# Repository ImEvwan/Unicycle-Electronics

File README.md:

# Unicycle-Electronics
Accessory and support electronics for the unicycle project

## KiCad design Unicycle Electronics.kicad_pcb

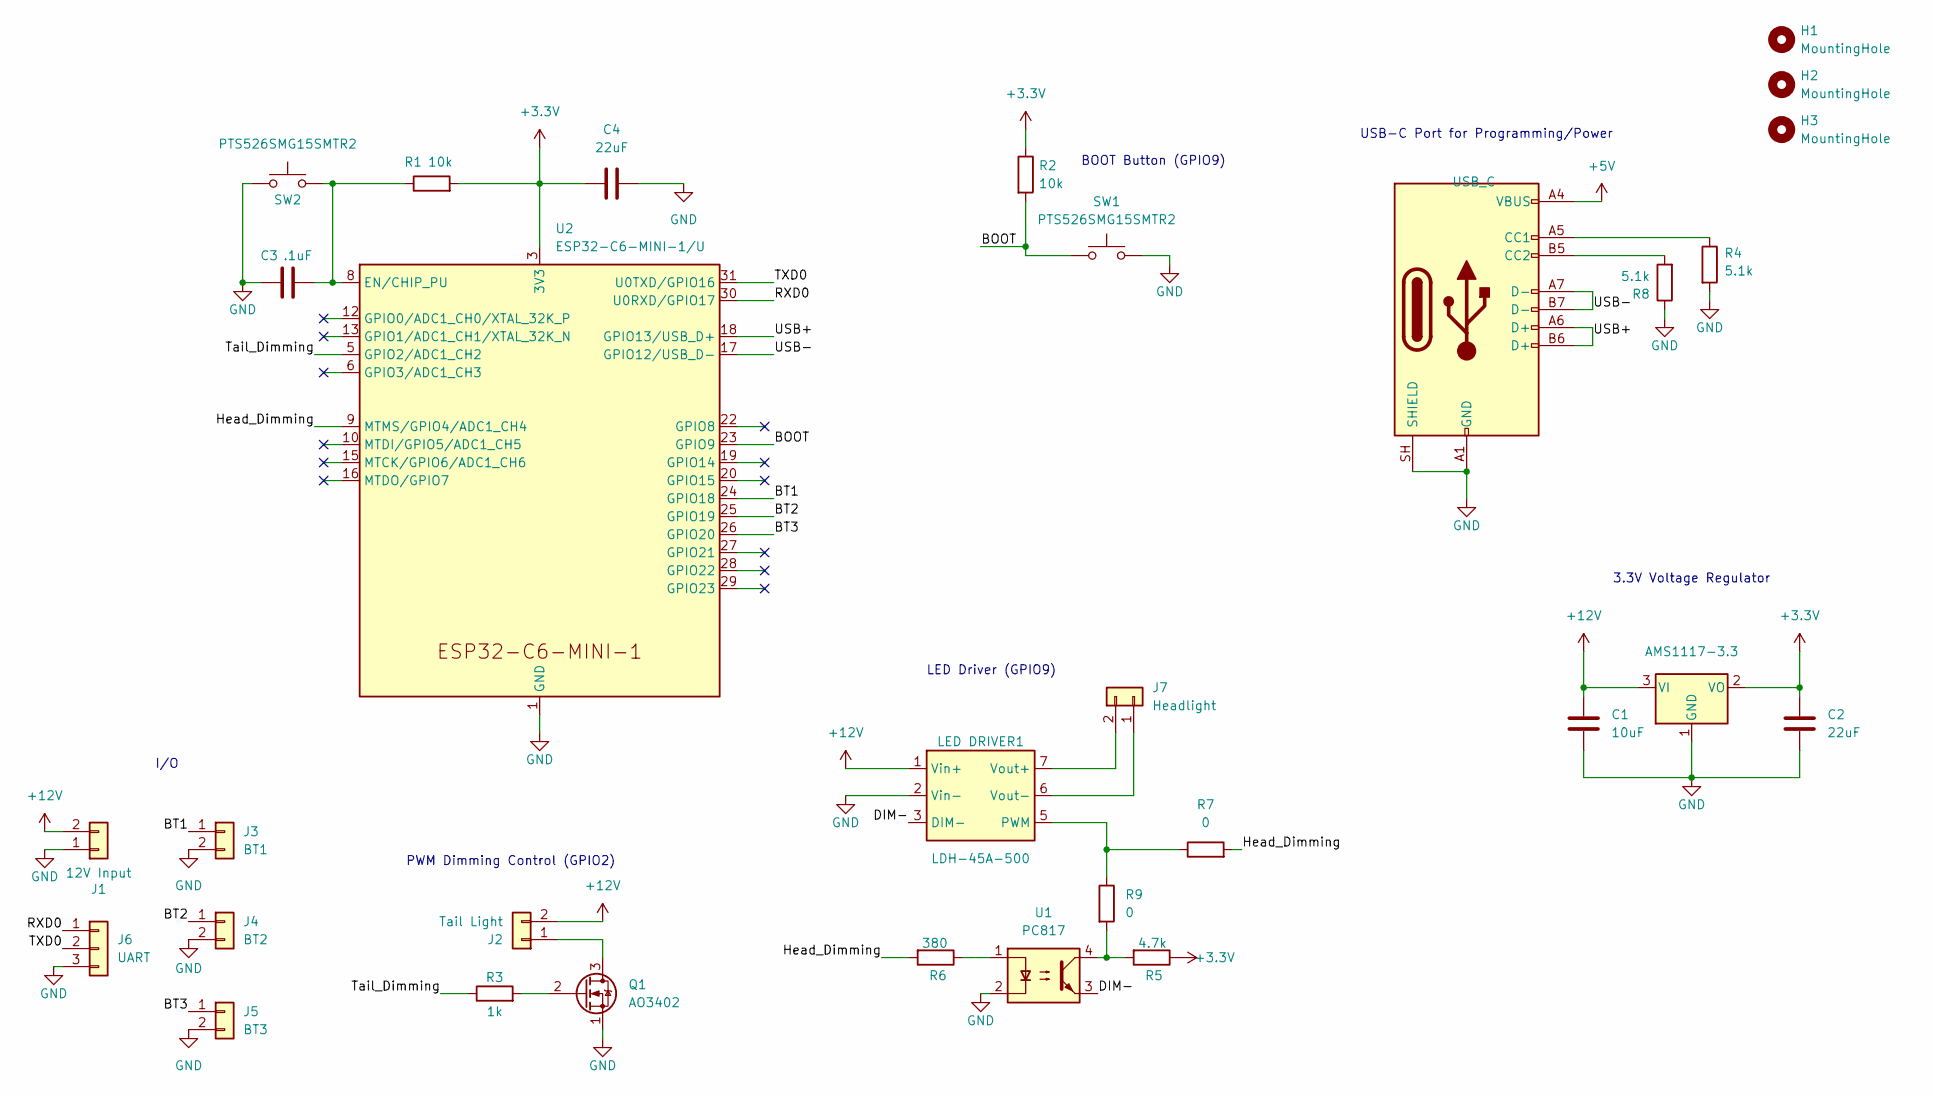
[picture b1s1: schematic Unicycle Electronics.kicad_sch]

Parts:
C1: 10uF; C_1206_3216Metric
C2, C4: 22uF; C_1206_3216Metric
C3: .1uF; C_1206_3216Metric
H1, H2, H3: MountingHole; MountingHole_3.2mm_M3_DIN965_Pad
J1: 12V Input; AMASS_XT30PW-M_1x02_P2.50mm_Horizontal
J2: Tail Light; AMASS_XT30PW-F_1x02_P2.50mm_Horizontal
J3: BT1; JST_PH_S2B-PH-K_1x02_P2.00mm_Horizontal
J4: BT2; JST_PH_S2B-PH-K_1x02_P2.00mm_Horizontal
J5: BT3; JST_PH_S2B-PH-K_1x02_P2.00mm_Horizontal
J6: UART; JST_PH_S3B-PH-K_1x03_P2.00mm_Horizontal
J7: Headlight; AMASS_XT30PW-F_1x02_P2.50mm_Horizontal
J10: USB_C; USB_C_Receptacle_GCT_USB4110
LED DRIVER1: LDH-45A-500
Q1: AO3402
R1, R2: 10k; R_1206_3216Metric
R3: 1k; R_1206_3216Metric
R4, R8: 5.1k; R_1206_3216Metric
R5: 4.7k; R_1206_3216Metric
R6: 380; R_1206_3216Metric
R7, R9: 0; R_1206_3216Metric
SW1, SW2: PTS526SMG15SMTR2; SW_SPST_SKQG_WithStem
U1: PC817; DIP-4_W7.62mm
U2: ESP32-C6-MINI-1/U; ESP32-C6-MINI-1
U3: AMS1117-3.3; SOT-223-3_TabPin2

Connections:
+3.3V: C2.1, C4.1, R1.2, R2.1, R5.1, U2.3 (3V3), U3.2 (VO)
+5V: J10.A4 (VBUS), J10.A9 (VBUS), J10.B4 (VBUS), J10.B9 (VBUS)
+12V: C1.1, J1.2, J2.2, LED DRIVER1.1 (Vin+), U3.3 (VI)
/BOOT: R2.2, SW1.1, U2.23 (GPIO9)
/BT1: J3.1, U2.24 (GPIO18)
/BT2: J4.1, U2.25 (GPIO19)
/BT3: J5.1, U2.26 (GPIO20)
/DIM-: LED DRIVER1.3 (DIM-), U1.3
/Head_Dimming: R6.2, R7.2, U2.9 (MTMS/GPIO4/ADC1_CH4)
/RXD0: J6.1, U2.30 (U0RXD/GPIO17)
/TXD0: J6.2, U2.31 (U0TXD/GPIO16)
/Tail_Dimming: R3.1, U2.5 (GPIO2/ADC1_CH2)
/USB+: J10.A6 (D+), J10.B6 (D+), U2.18 (GPIO13/USB_D+)
/USB-: J10.A7 (D-), J10.B7 (D-), U2.17 (GPIO12/USB_D-)
GND: C1.2, C2.2, C3.1, C4.2, J1.1, J3.2, J4.2, J5.2, J6.3, J10.A1 (GND), J10.A12 (GND), J10.B1 (GND), J10.B12 (GND), J10.SH (SHIELD), LED DRIVER1.2 (Vin-), Q1.1 (S), R4.2, R8.1, SW1.2, SW2.1, U1.2, U2.1 (GND), U2.2 (GND), U2.11 (GND), U2.14 (GND), U2.36 (GND), U2.37 (GND), U2.38 (GND), U2.39 (GND), U2.40 (GND), U2.41 (GND), U2.42 (GND), U2.43 (GND), U2.44 (GND), U2.45 (GND), U2.46 (GND), U2.47 (GND), U2.48 (GND), U2.49 (GND), U2.50 (GND), U2.51 (GND), U2.52 (GND), U2.53 (GND), U3.1 (GND)
unnamed: J2.1, Q1.3 (D)
unnamed: J7.2 (Pin_1), LED DRIVER1.7 (Vout+)
unnamed: J7.1 (Pin_2), LED DRIVER1.6 (Vout-)
unnamed: J10.A5 (CC1), R4.1
unnamed: J10.B5 (CC2), R8.2
unnamed: LED DRIVER1.5 (PWM), R7.1, R9.1
unnamed: Q1.2 (G), R3.2
unnamed: R5.2, R9.2, U1.4
unnamed: R6.1, U1.1
unnamed: C3.2, R1.1, SW2.2, U2.8 (EN/CHIP_PU)

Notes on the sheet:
I/O
PWM Dimming Control (GPIO2)
3.3V Voltage Regulator
USB-C Port for Programming/Power
LED Driver (GPIO9)
BOOT Button (GPIO9)

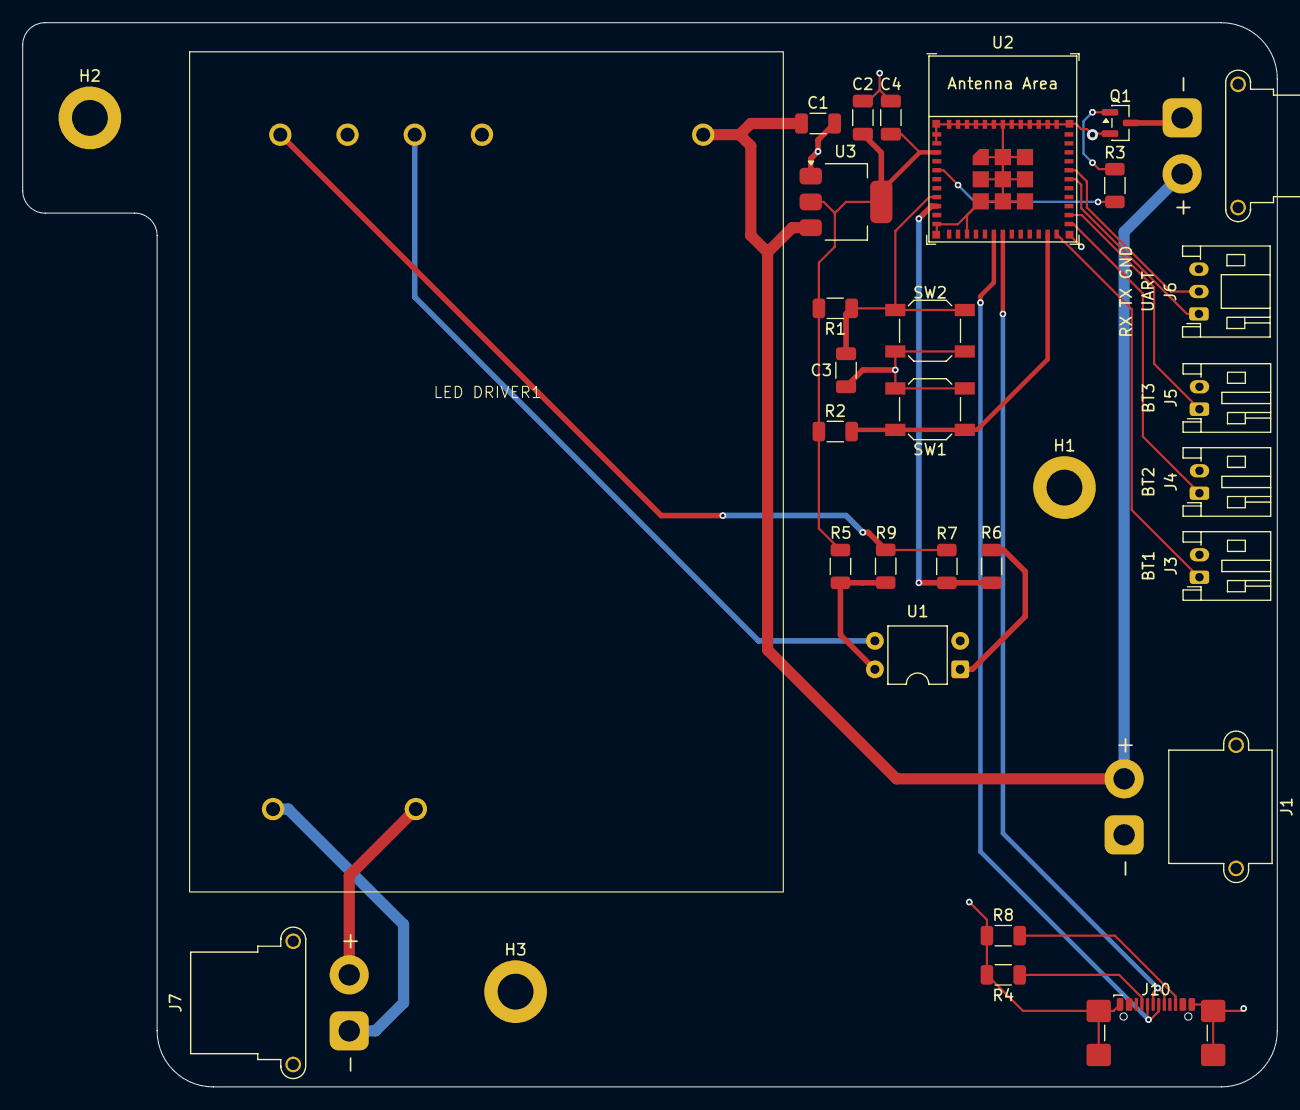
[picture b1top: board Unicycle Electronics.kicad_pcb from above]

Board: 2 copper layers, 112.0 x 95.0 mm, 31 parts (0 on the bottom side), 25 nets.

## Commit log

2025-11-20 Added gitignore
2025-11-20 Added Library
2025-12-04 Initial mock
2025-12-05 Schematic updates
    Cleaned it up, added nets
    TODO:
    Change Diodes to some sort of connector, the LEDs are not on the PCB, they need to be plugged in
    3.3v regulator for ESP32
    BOOT and EN buttons for ESP32
    Add PWM Dimming pins to LED driver
2026-01-28 schematic update
    This is what I have so far—let me know if you need any changes or want me to add anything.
2026-01-29 Updated TODO list, Changed EN button
2026-02-02 Schematic Update
    Worked on some TODO List
2026-02-24 Schematic Update
    Finished the TODO List
2026-03-02 Schematic Update
    Cleaned up the schematic
2026-03-02 Finished Schematic, Started PCB
2026-03-02 PCB Revision 1
2026-03-03 Added mounting holes, updated footprints
2026-03-04 pre mfg
2026-03-04 Finished PCB
2026-04-09 Fixed footprint and routing for tail light MOSFET
    gate and source were switched, incorrect footprint :(
2026-04-29 updated 3d models
